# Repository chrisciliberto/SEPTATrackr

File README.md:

# SEPTATrackr
# Test Heading

this is a paragraph
## SubHeading

this is a sub paragraph

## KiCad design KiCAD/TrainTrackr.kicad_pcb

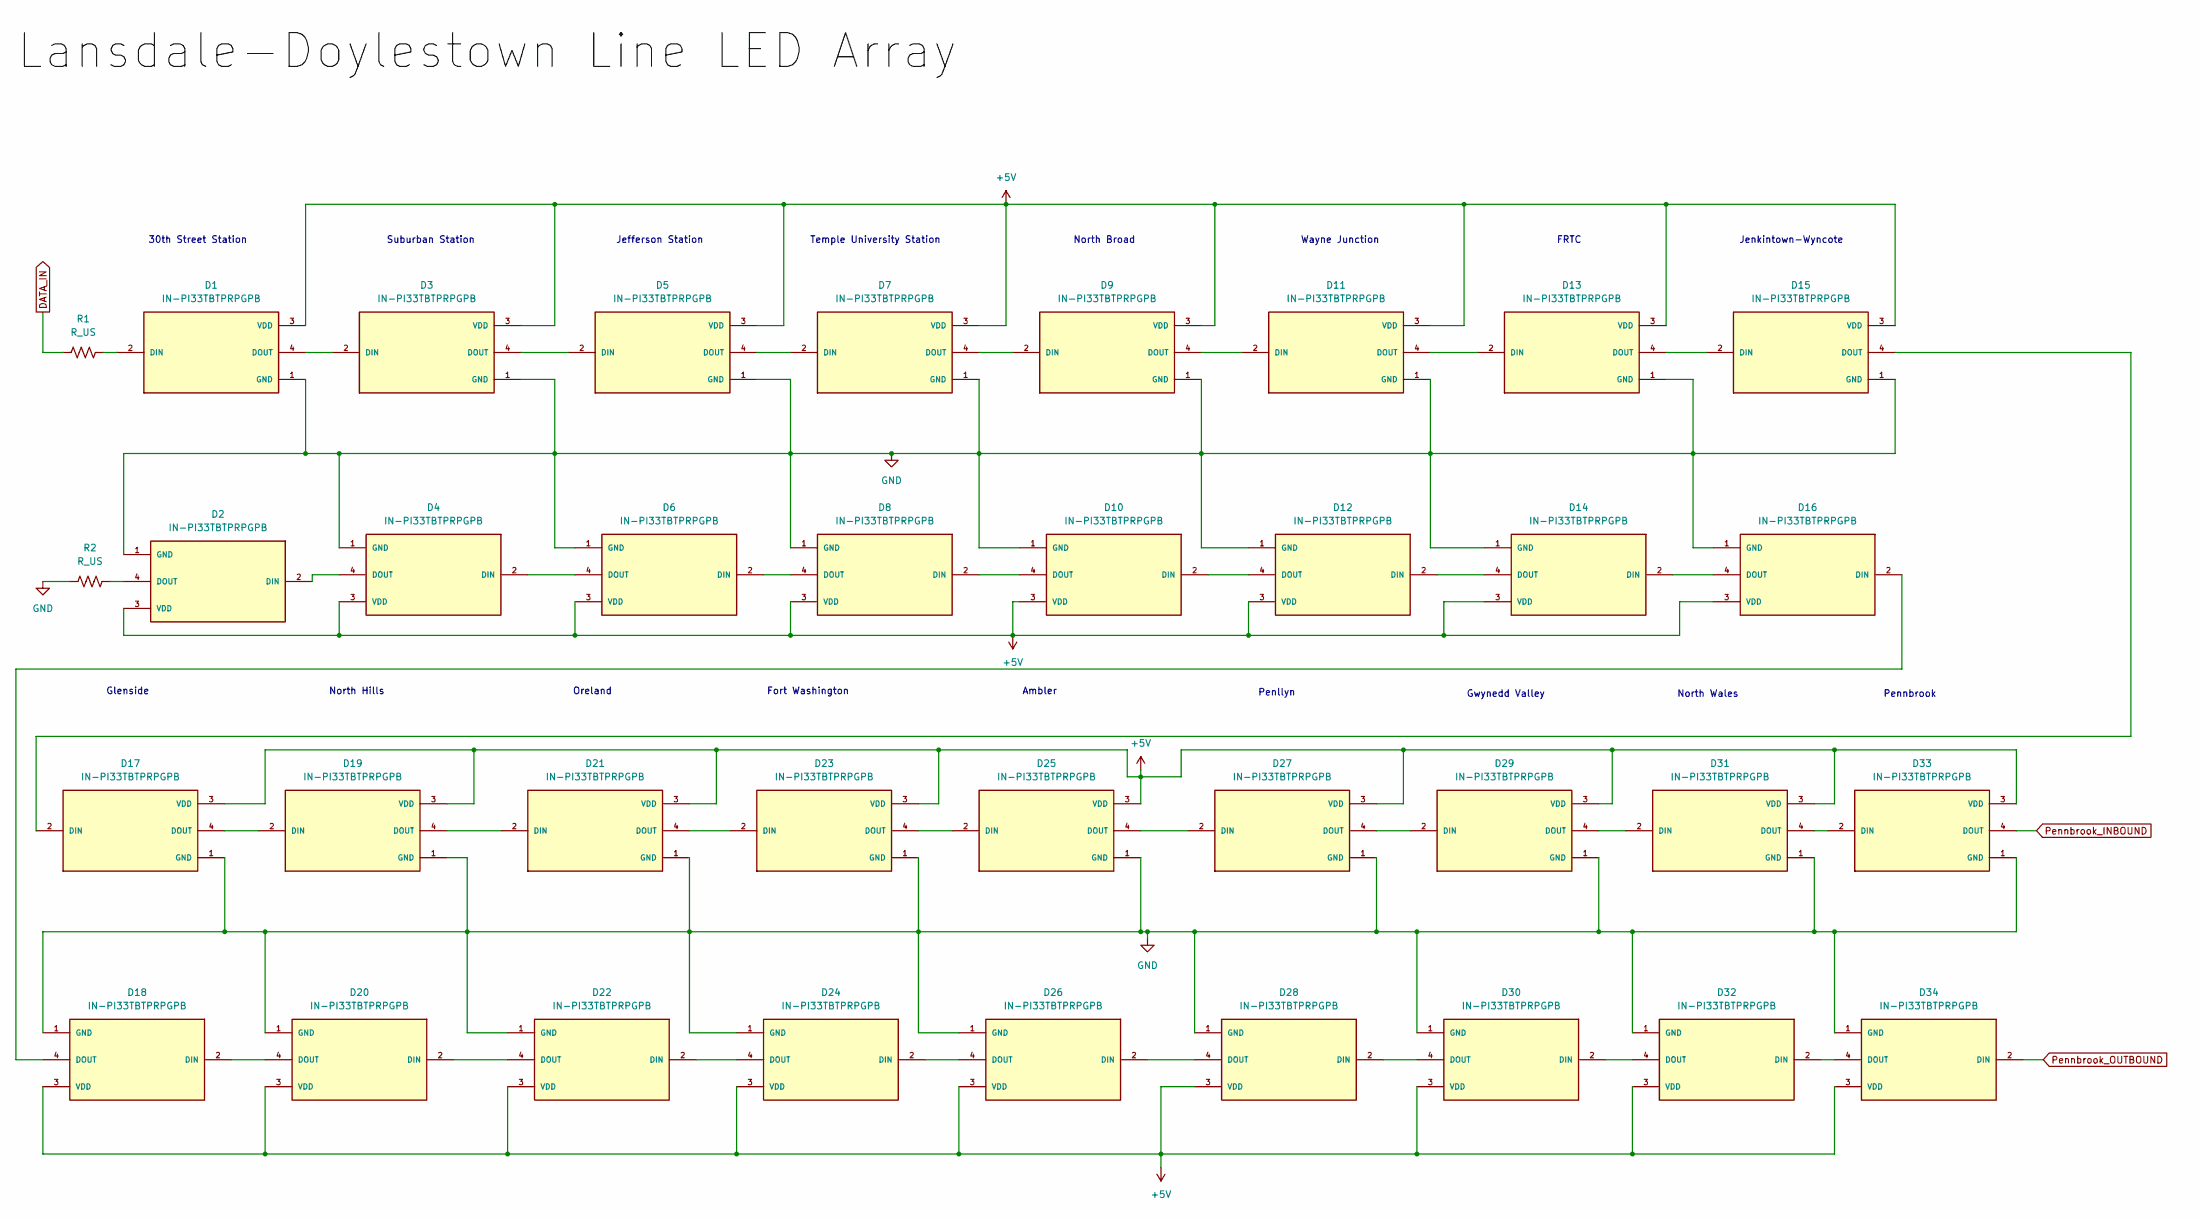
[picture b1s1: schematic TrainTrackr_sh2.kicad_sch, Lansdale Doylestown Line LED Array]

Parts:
D1, D2, D3, D4, D5, D6, D7, D8, D9, D10, D11, D12, D13, D14, D15, D16, D17, D18, D19, D20, D21, D22, D23, D24, D25, D26, D27, D28, D29, D30, D31, D32, D33, D34: IN-PI33TBTPRPGPB; LED_IN-PI33TBTPRPGPB; PARTREV 1.2
R1, R2: R_US; R_0603_1608Metric_Pad0.98x0.95mm_HandSolder

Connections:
+5V: D1.3 (VDD), D2.3 (VDD), D3.3 (VDD), D4.3 (VDD), D5.3 (VDD), D6.3 (VDD), D7.3 (VDD), D8.3 (VDD), D9.3 (VDD), D10.3 (VDD), D11.3 (VDD), D12.3 (VDD), D13.3 (VDD), D14.3 (VDD), D15.3 (VDD), D16.3 (VDD), D17.3 (VDD), D18.3 (VDD), D19.3 (VDD), D20.3 (VDD), D21.3 (VDD), D22.3 (VDD), D23.3 (VDD), D24.3 (VDD), D25.3 (VDD), D26.3 (VDD), D27.3 (VDD), D28.3 (VDD), D29.3 (VDD), D30.3 (VDD), D31.3 (VDD), D32.3 (VDD), D33.3 (VDD), D34.3 (VDD); also elsewhere on the board
DATA_IN: R1.1; also elsewhere on the board
GND: D1.1 (GND), D2.1 (GND), D3.1 (GND), D4.1 (GND), D5.1 (GND), D6.1 (GND), D7.1 (GND), D8.1 (GND), D9.1 (GND), D10.1 (GND), D11.1 (GND), D12.1 (GND), D13.1 (GND), D14.1 (GND), D15.1 (GND), D16.1 (GND), D17.1 (GND), D18.1 (GND), D19.1 (GND), D20.1 (GND), D21.1 (GND), D22.1 (GND), D23.1 (GND), D24.1 (GND), D25.1 (GND), D26.1 (GND), D27.1 (GND), D28.1 (GND), D29.1 (GND), D30.1 (GND), D31.1 (GND), D32.1 (GND), D33.1 (GND), D34.1 (GND), R2.1; also elsewhere on the board
unnamed: D1.2 (DIN), R1.2
unnamed: D1.4 (DOUT), D3.2 (DIN)
unnamed: D2.2 (DIN), D4.4 (DOUT)
unnamed: D2.4 (DOUT), R2.2
unnamed: D3.4 (DOUT), D5.2 (DIN)
unnamed: D4.2 (DIN), D6.4 (DOUT)
unnamed: D5.4 (DOUT), D7.2 (DIN)
unnamed: D6.2 (DIN), D8.4 (DOUT)
unnamed: D7.4 (DOUT), D9.2 (DIN)
unnamed: D10.2 (DIN), D12.4 (DOUT)
unnamed: D8.2 (DIN), D10.4 (DOUT)
unnamed: D9.4 (DOUT), D11.2 (DIN)
unnamed: D11.4 (DOUT), D13.2 (DIN)
unnamed: D12.2 (DIN), D14.4 (DOUT)
unnamed: D13.4 (DOUT), D15.2 (DIN)
unnamed: D14.2 (DIN), D16.4 (DOUT)
unnamed: D15.4 (DOUT), D17.2 (DIN)
unnamed: D16.2 (DIN), D18.4 (DOUT)
unnamed: D17.4 (DOUT), D19.2 (DIN)
unnamed: D18.2 (DIN), D20.4 (DOUT)
unnamed: D19.4 (DOUT), D21.2 (DIN)
unnamed: D20.2 (DIN), D22.4 (DOUT)
unnamed: D21.4 (DOUT), D23.2 (DIN)
unnamed: D22.2 (DIN), D24.4 (DOUT)
unnamed: D23.4 (DOUT), D25.2 (DIN)
unnamed: D24.2 (DIN), D26.4 (DOUT)
unnamed: D25.4 (DOUT), D27.2 (DIN)
unnamed: D26.2 (DIN), D28.4 (DOUT)
unnamed: D27.4 (DOUT), D29.2 (DIN)
unnamed: D28.2 (DIN), D30.4 (DOUT)
unnamed: D29.4 (DOUT), D31.2 (DIN)
unnamed: D30.2 (DIN), D32.4 (DOUT)
unnamed: D31.4 (DOUT), D33.2 (DIN)
unnamed: D32.2 (DIN), D34.4 (DOUT)
Pennbrook_INBOUND: D33.4 (DOUT); also elsewhere on the board
Pennbrook_OUTBOUND: D34.2 (DIN); also elsewhere on the board

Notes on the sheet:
FRTC
30th Street Station
Fort Washington
Penllyn
North Hills
Jenkintown-Wyncote
Oreland
Temple University Station
Suburban Station
North Wales
Gwynedd Valley
Wayne Junction
Jefferson Station
North Broad
Ambler
Pennbrook
Glenside

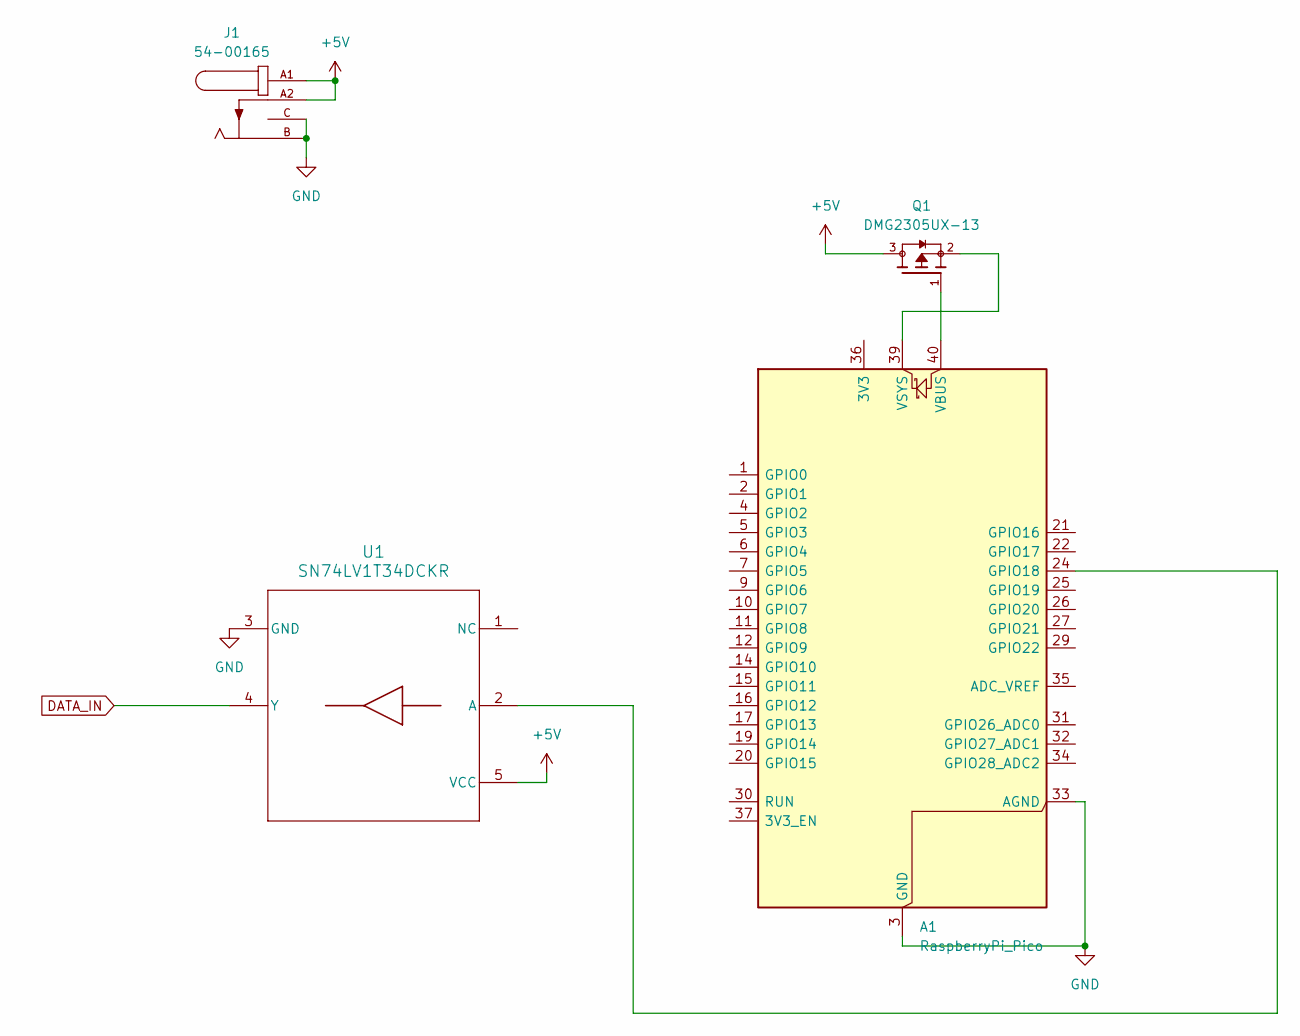
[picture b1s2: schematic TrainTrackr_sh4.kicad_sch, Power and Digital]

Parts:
A1: RaspberryPi_Pico; RaspberryPi_Pico_W_SMD_HandSolder
J1: 54-00165; TENSILITY_54-00165; PARTREV A
Q1: DMG2305UX-13; train; PARTREV 09/2018
U1: SN74LV1T34DCKR; DCK0005A_L

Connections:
+5V: J1.A1, J1.A2, Q1.3, U1.5 (VCC); also elsewhere on the board
DATA_IN: U1.4 (Y); also elsewhere on the board
GND: A1.3 (GND), A1.8 (GND), A1.13 (GND), A1.18 (GND), A1.23 (GND), A1.28 (GND), A1.33 (AGND), A1.38 (GND), J1.B, J1.C, U1.3 (GND); also elsewhere on the board
unnamed: A1.24 (GPIO18), U1.2 (A)
unnamed: A1.40 (VBUS), Q1.1
unnamed: A1.39 (VSYS), Q1.2

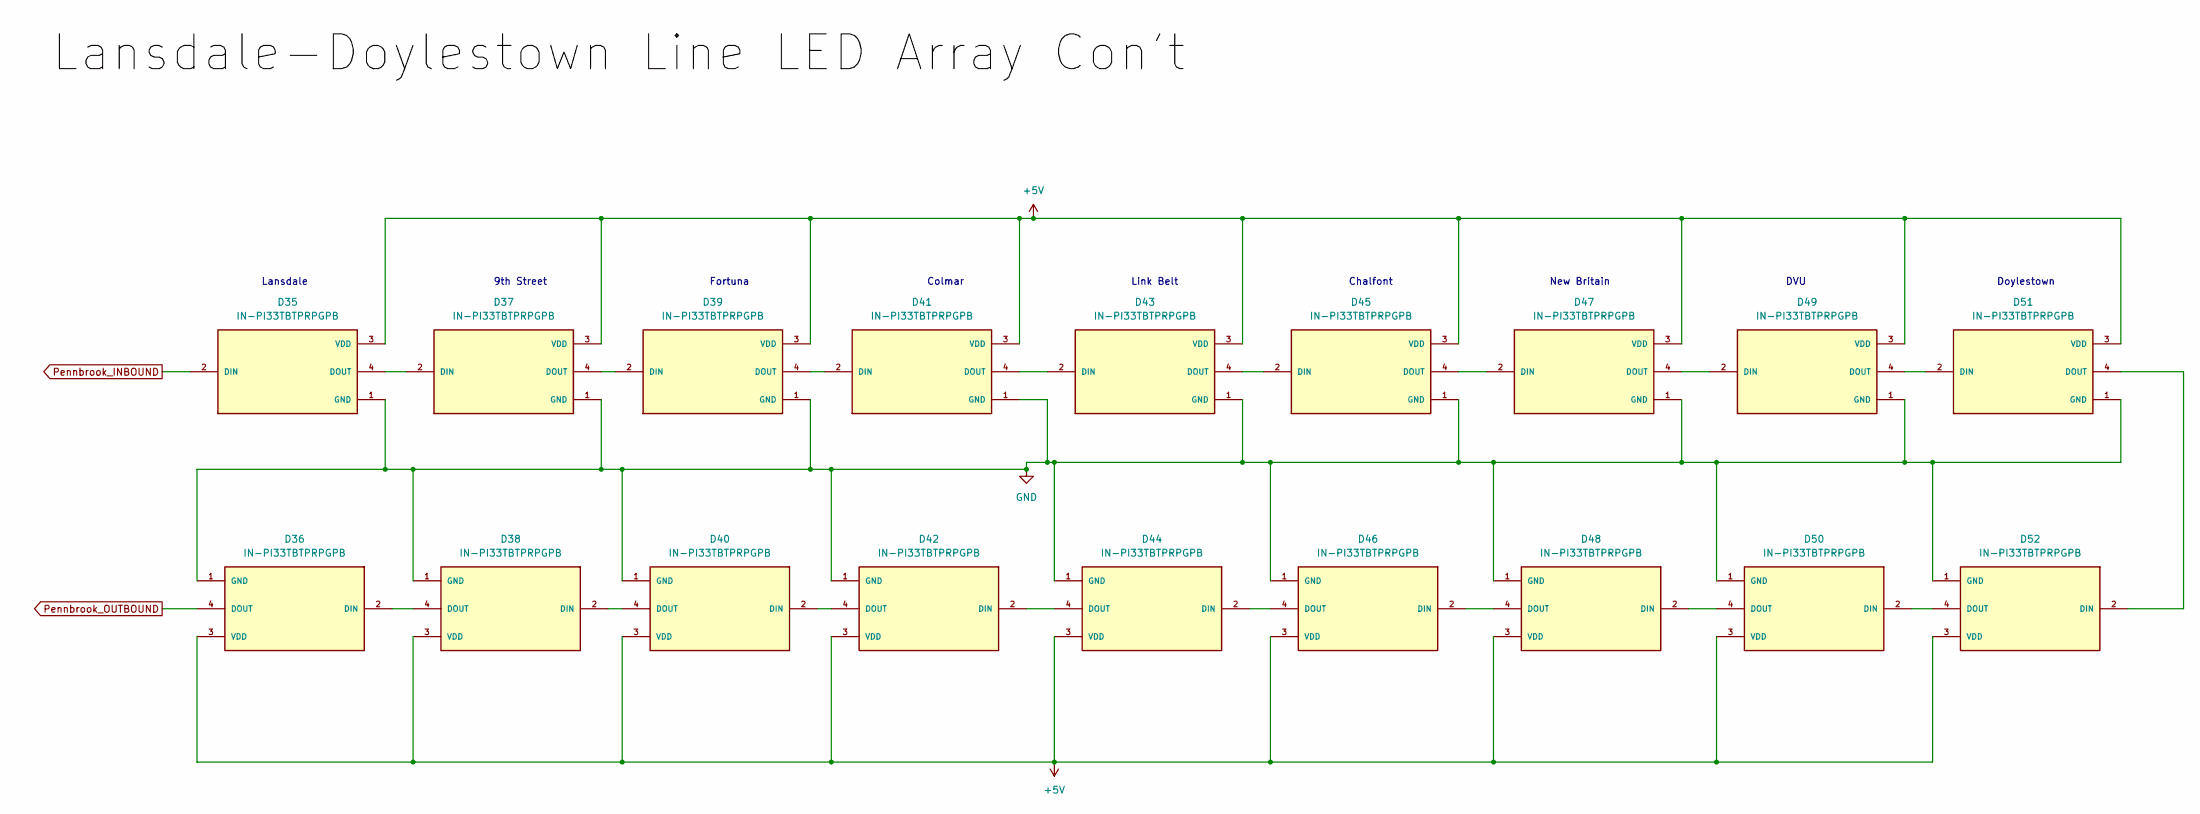
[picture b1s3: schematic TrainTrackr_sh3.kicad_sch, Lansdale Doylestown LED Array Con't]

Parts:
D35, D36, D37, D38, D39, D40, D41, D42, D43, D44, D45, D46, D47, D48, D49, D50, D51, D52: IN-PI33TBTPRPGPB; LED_IN-PI33TBTPRPGPB; PARTREV 1.2

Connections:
+5V: D35.3 (VDD), D36.3 (VDD), D37.3 (VDD), D38.3 (VDD), D39.3 (VDD), D40.3 (VDD), D41.3 (VDD), D42.3 (VDD), D43.3 (VDD), D44.3 (VDD), D45.3 (VDD), D46.3 (VDD), D47.3 (VDD), D48.3 (VDD), D49.3 (VDD), D50.3 (VDD), D51.3 (VDD), D52.3 (VDD); also elsewhere on the board
GND: D35.1 (GND), D36.1 (GND), D37.1 (GND), D38.1 (GND), D39.1 (GND), D40.1 (GND), D41.1 (GND), D42.1 (GND), D43.1 (GND), D44.1 (GND), D45.1 (GND), D46.1 (GND), D47.1 (GND), D48.1 (GND), D49.1 (GND), D50.1 (GND), D51.1 (GND), D52.1 (GND); also elsewhere on the board
unnamed: D35.4 (DOUT), D37.2 (DIN)
unnamed: D36.2 (DIN), D38.4 (DOUT)
unnamed: D37.4 (DOUT), D39.2 (DIN)
unnamed: D38.2 (DIN), D40.4 (DOUT)
unnamed: D39.4 (DOUT), D41.2 (DIN)
unnamed: D40.2 (DIN), D42.4 (DOUT)
unnamed: D41.4 (DOUT), D43.2 (DIN)
unnamed: D42.2 (DIN), D44.4 (DOUT)
unnamed: D43.4 (DOUT), D45.2 (DIN)
unnamed: D44.2 (DIN), D46.4 (DOUT)
unnamed: D45.4 (DOUT), D47.2 (DIN)
unnamed: D46.2 (DIN), D48.4 (DOUT)
unnamed: D47.4 (DOUT), D49.2 (DIN)
unnamed: D48.2 (DIN), D50.4 (DOUT)
unnamed: D49.4 (DOUT), D51.2 (DIN)
unnamed: D50.2 (DIN), D52.4 (DOUT)
unnamed: D51.4 (DOUT), D52.2 (DIN)
Pennbrook_INBOUND: D35.2 (DIN); also elsewhere on the board
Pennbrook_OUTBOUND: D36.4 (DOUT); also elsewhere on the board

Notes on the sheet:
Link Belt
DVU
Lansdale
Fortuna
Doylestown
9th Street
Chalfont
New Britain
Colmar

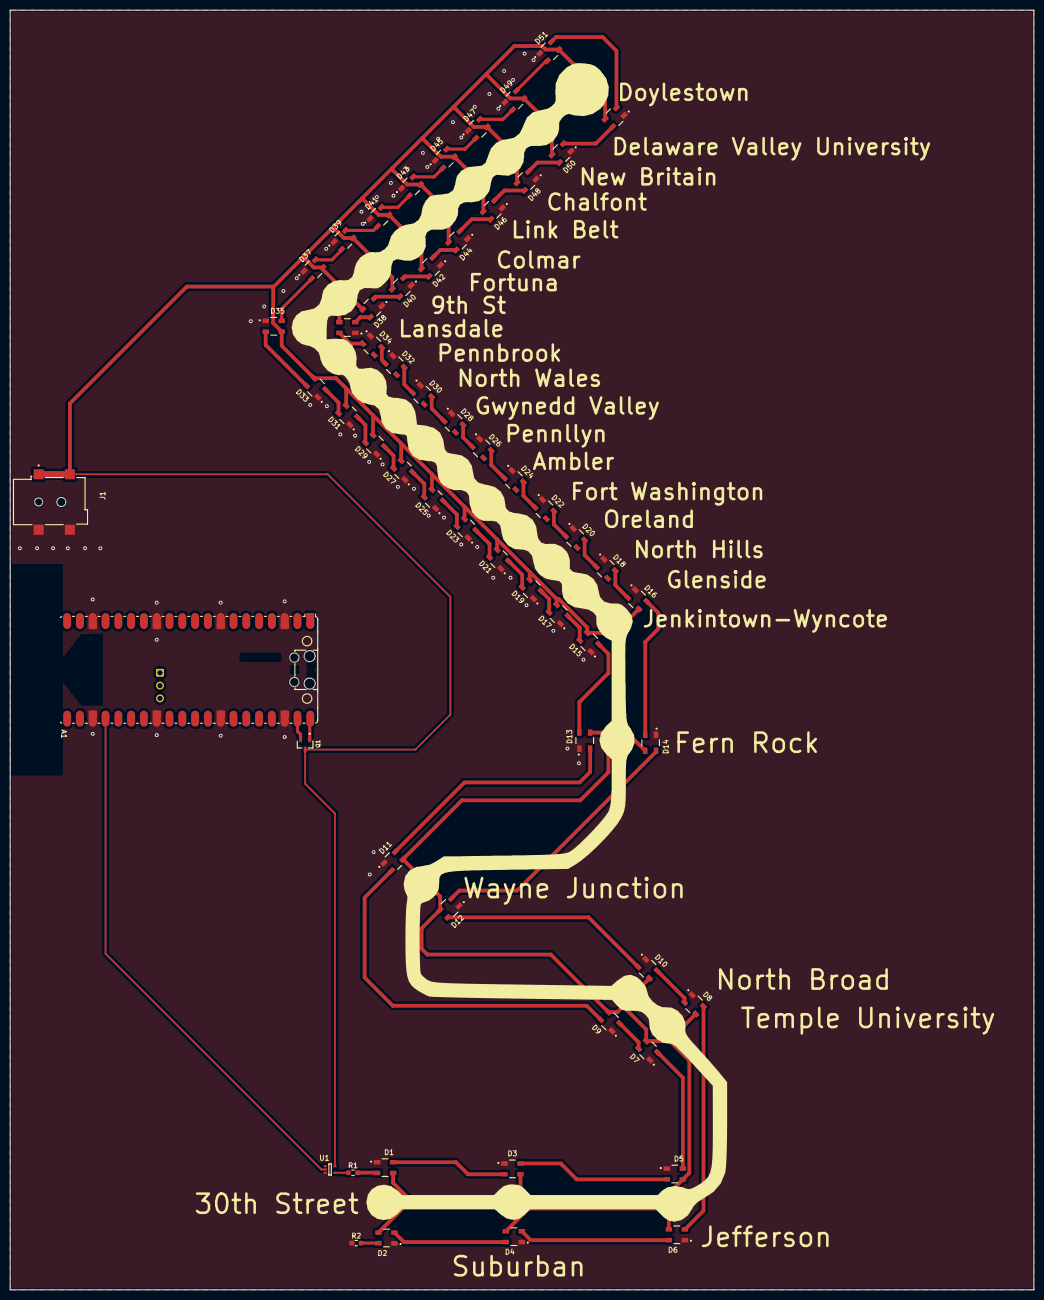
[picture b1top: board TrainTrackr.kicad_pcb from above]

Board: 2 copper layers, 203.2 x 254.0 mm, 58 parts (0 on the bottom side), 59 nets.

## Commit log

2025-01-07 added original kicad documents
2025-01-07 updated sch
2025-01-08 silk screen png and sch updates
2025-01-09 updated layout and sch
2025-01-09 sch layout update
